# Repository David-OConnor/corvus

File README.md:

# Corvus: Small UAS flight controller firmware

todo: Fill out this README

This mainly exists as a code demo, although is mostly functional for quadcopter rate-control ("acro") flight, when paired with specific hardware. There is nascent code to support fixed-wing flight, but it is incomplete and untested.

It uses [RTIC](https://rtic.rs/2/book/en/) to manage control flow, via interrupts.

[Video of a flight](https://www.youtube.com/watch?v=sHvgl4OjA7A) (OSD not shown)

## Overview
This firmware is tied to specific hardware configurations. It runs on STM32G4 and STM32H743 flight controllers. (AnyLeaf boards). It requires specific hardware, currently:

 - ICM426xx IMU (SPI)
 - DPS310 barometeric altimeter (I2c)
 - UART GPS using the UBLOX protocol
 - MSP Displayport OSD (e.g. DJI O3, WTFOS etc)
 - DSHOT ESC motor controllers
 - ELRS (CRSF) controls (UART)
 - WIP support for CAN GPS, external AHRS, and controls

It is in either a flyable, or close to flyable state if paired with compatible hardware, using acro mode only. Code is written for semi-autonomous flight modes, but these are not working.

Its primary flight control model is attitude-based. Its acro mode is based on this as well, setting the attitude target based on rate controls, vice direct gyro reads. This results in higher latency than traditional gyro-based acro modes, but is less sensitive to tuning. It decouples control inputs from response.

See the [accompanying Preflight repo](https://github.com/David-OConnor/preflight/) for PC software that connects via USB to view system status, and configure the UAS.

See [the accompanying AHRS library](https://github.com/David-OConnor/ahrs), which it uses as a dependency,
for the attitude heading-reference system.

See [this DroneCAN library](https://github.com/David-OConnor/dronecan) for interaction with CAN peripherals.

See descriptions in individual modules for their function.

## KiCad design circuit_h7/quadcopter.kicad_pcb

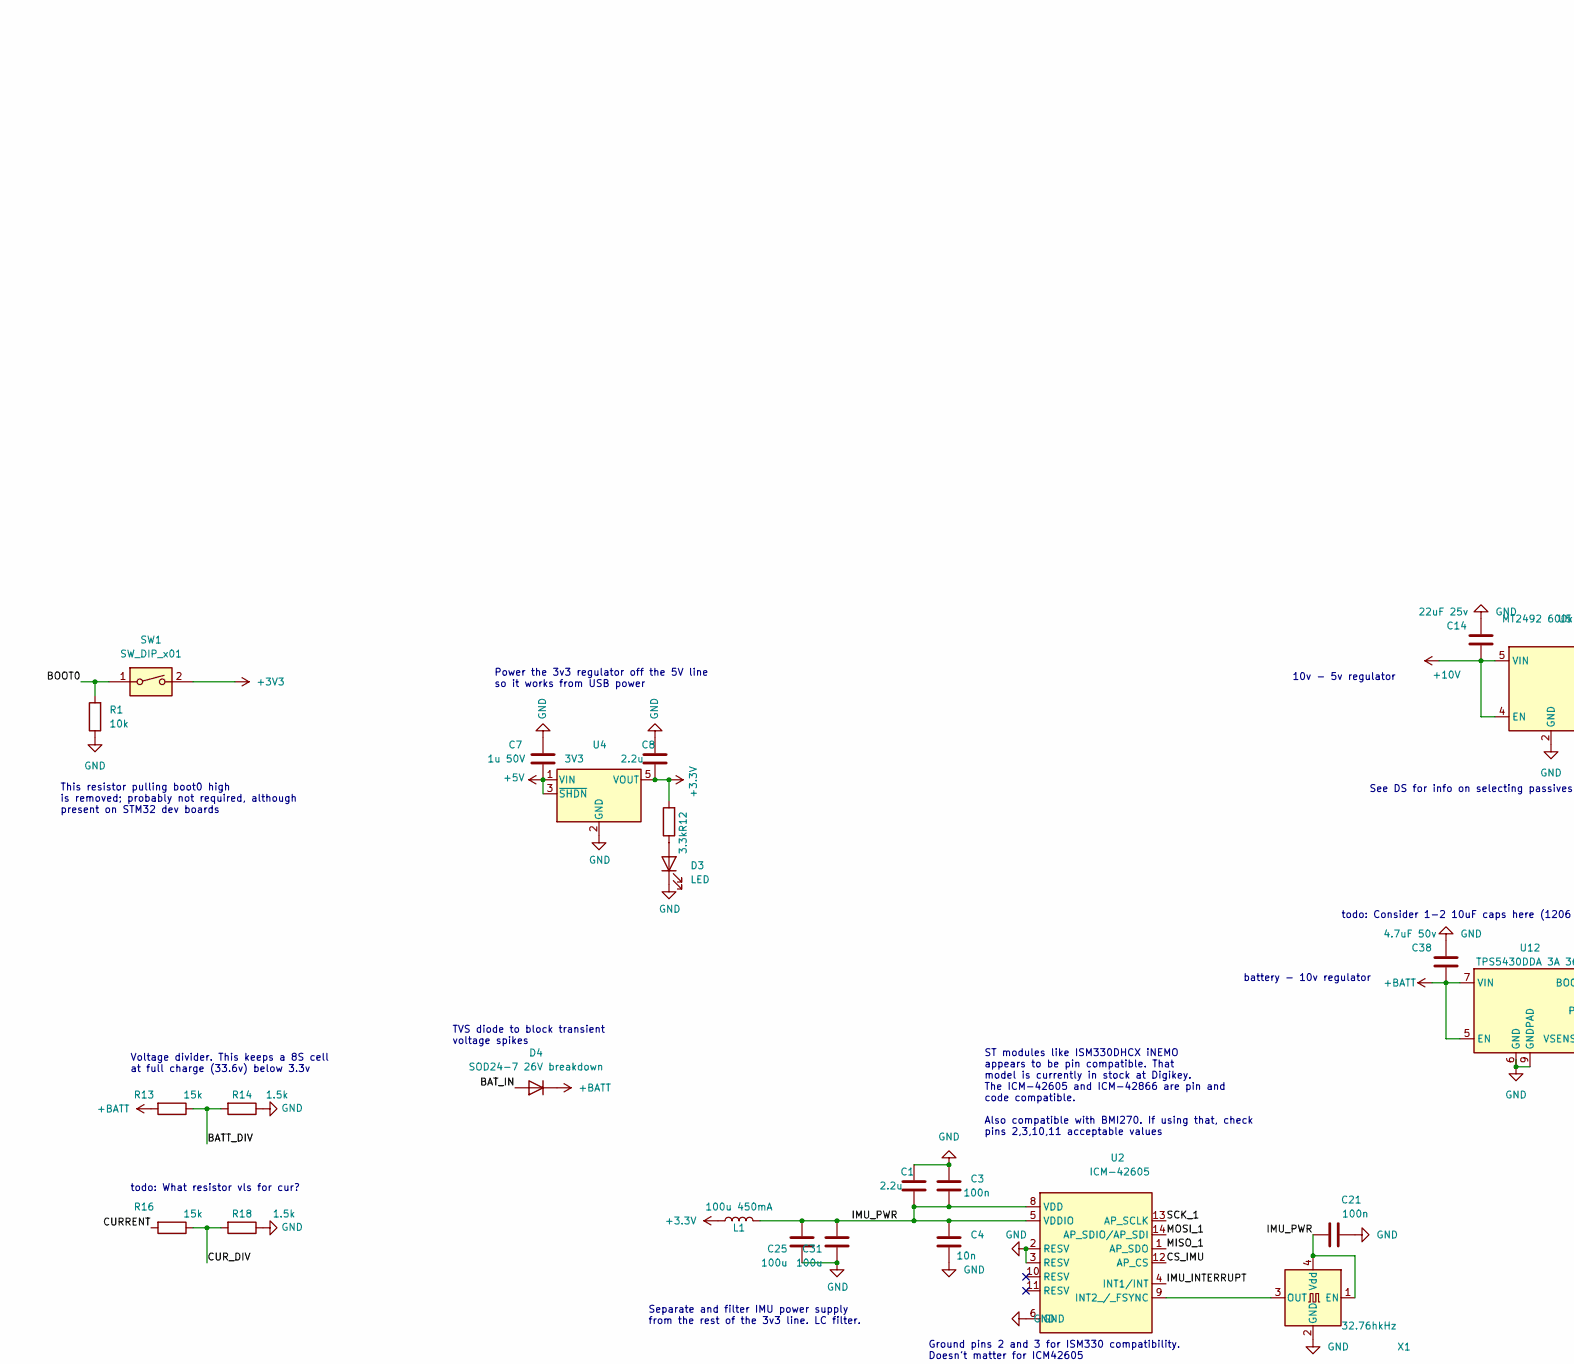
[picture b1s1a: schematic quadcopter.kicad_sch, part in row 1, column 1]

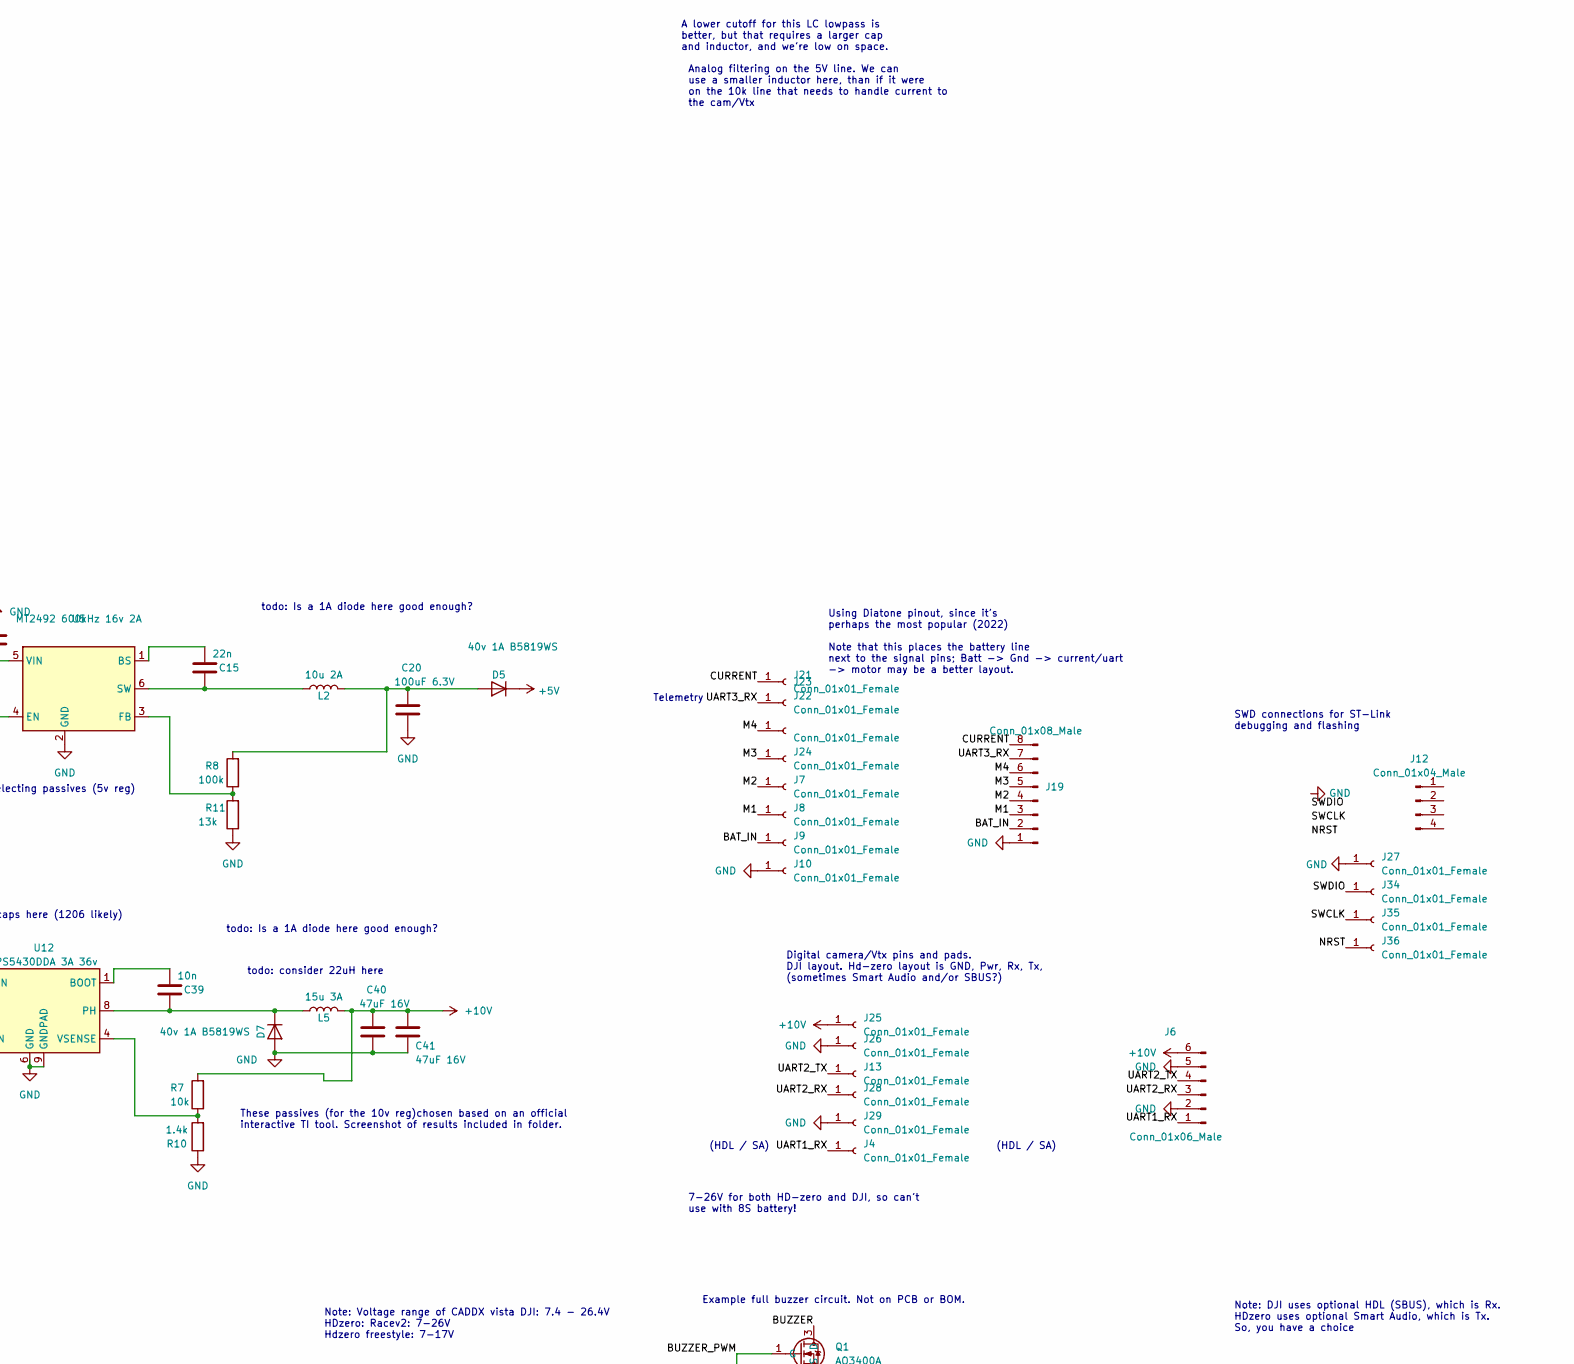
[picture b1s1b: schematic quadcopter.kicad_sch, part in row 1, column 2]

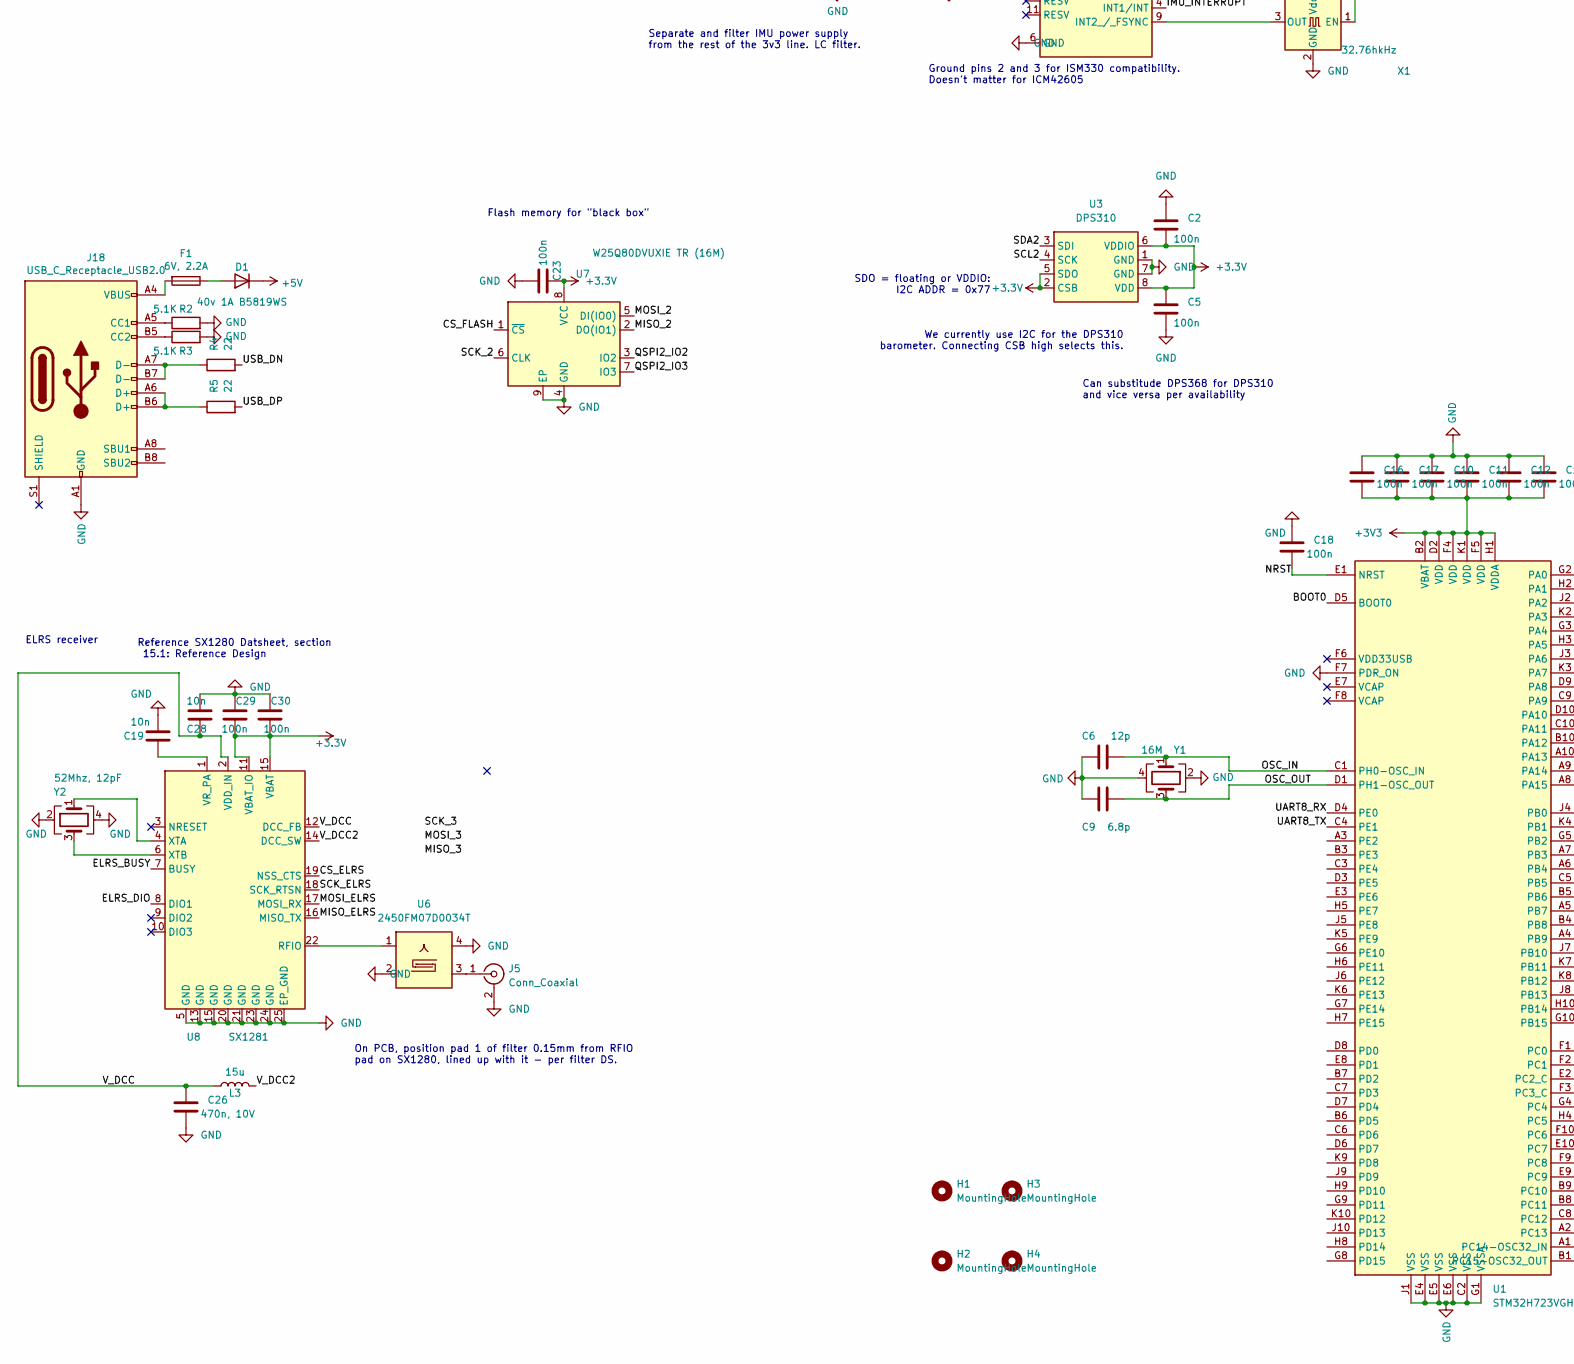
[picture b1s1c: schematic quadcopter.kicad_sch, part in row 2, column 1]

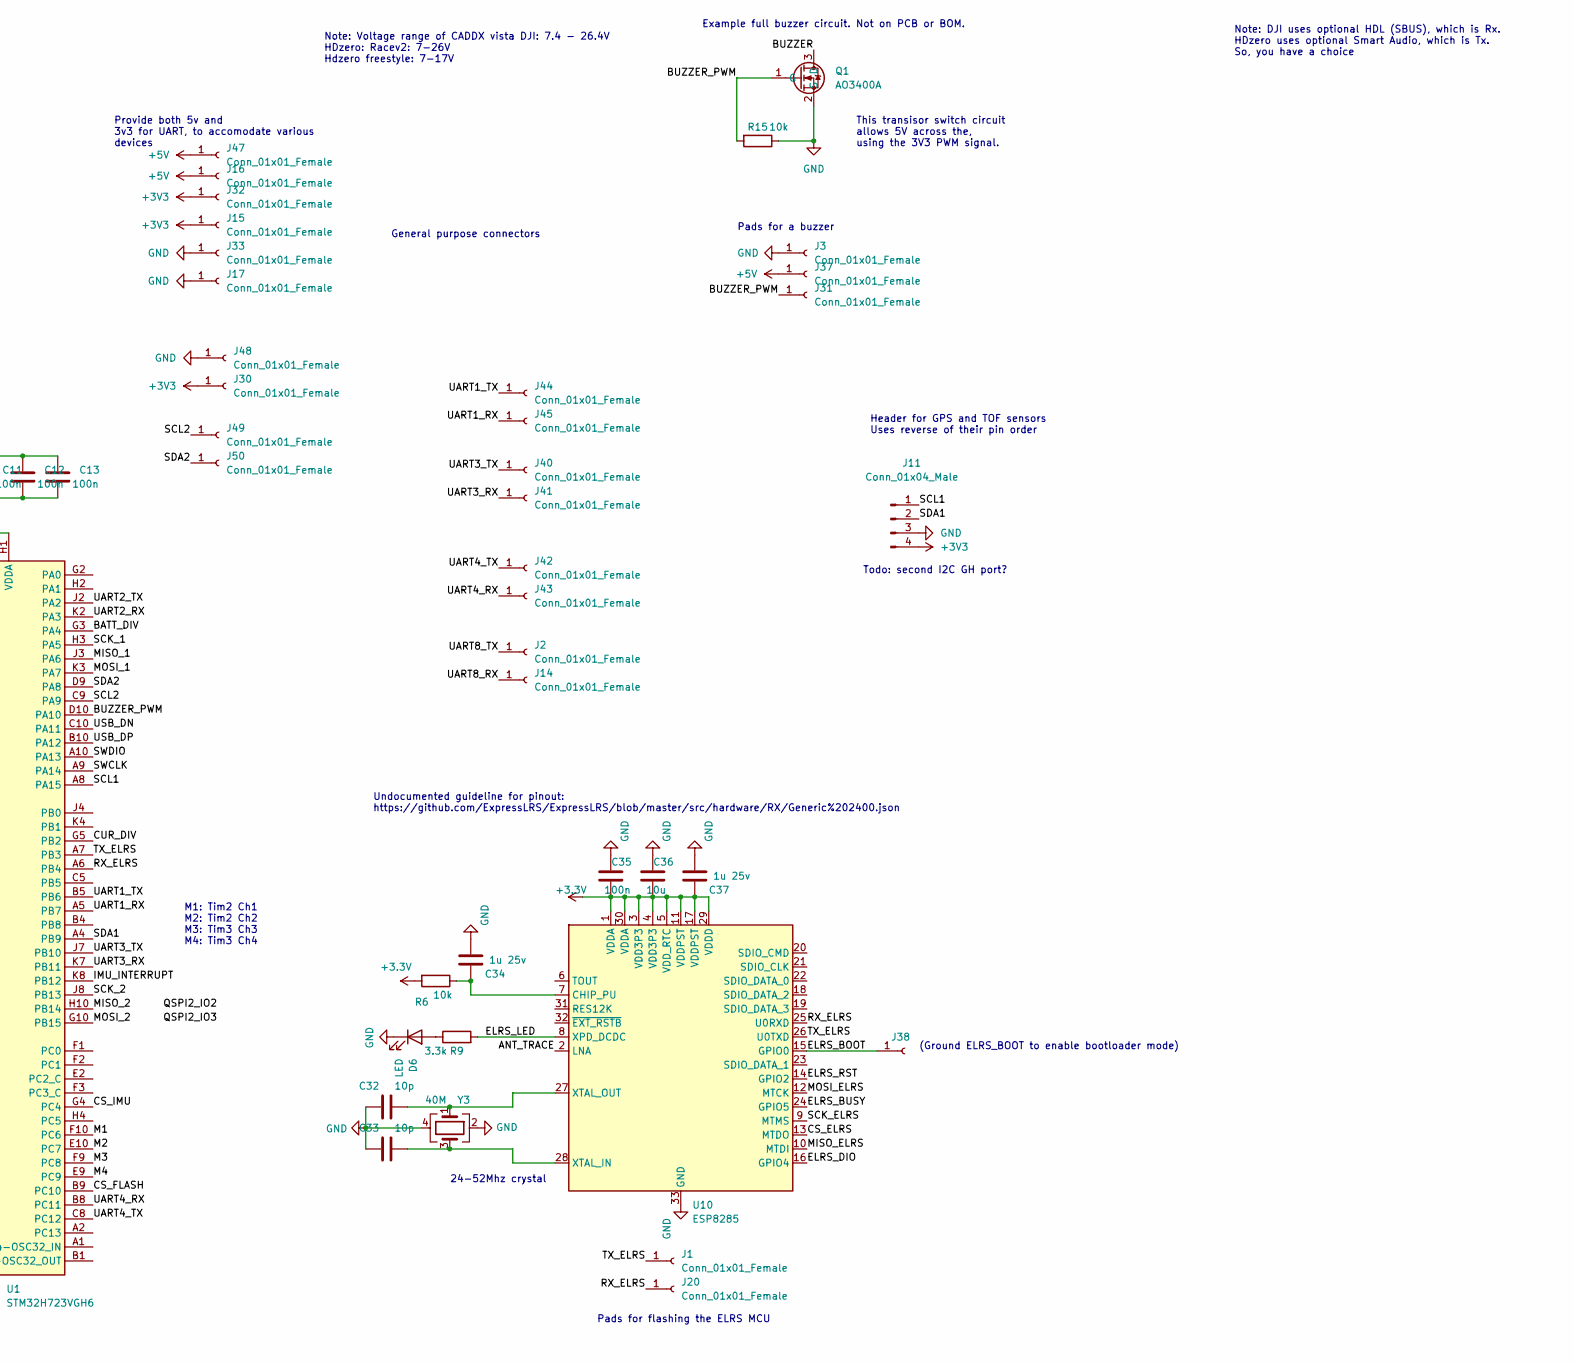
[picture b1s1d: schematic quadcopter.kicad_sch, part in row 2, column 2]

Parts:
C1, C8: 2.2u; C_0402_1005Metric; LCSC C12530
C2, C3, C5, C10, C11, C12, C13, C16, C17, C18, C21, C23, C29, C30, C35: 100n; C_0402_1005Metric; LCSC C1525
C4, C19, C28, C39: 10n; C_0402_1005Metric; LCSC C15195
C6: 12p; C_0402_1005Metric; LCSC C1547
C7: 1u 50V; C_0603_1608Metric; LCSC C15849
C9: 6.8p; C_0402_1005Metric; LCSC C1576
C14: 22uF 25v; C_0805_2012Metric; LCSC C602037
C15: 22n; C_0402_1005Metric; LCSC C1532
C20: 100uF 6.3V; C_1206_3216Metric; LCSC C15008
C25, C31: 100u; C_0805_2012Metric; LCSC C141660
C26: 470n, 10V; C_0402_1005Metric; LCSC C47339
C32, C33: 10p; C_0402_1005Metric; LCSC C32949
C34, C37: 1u 25v; C_0402_1005Metric; LCSC C52923
C36: 10u; C_0402_1005Metric; LCSC C15525
C38: 4.7uF 50v; C_0805_2012Metric; LCSC C98192
C40, C41: 47uF 16V; C_1210_3225Metric; LCSC C412625
D1, D5, D7: 40v 1A B5819WS; D_SOD-323; LCSC C22624
D3: LED; LED_0603_1608Metric; LCSC C205443
D4: SOD24-7 26V breakdown; D_SOD-323; Digikey 31-SD24-7TR-ND
D6: LED; LED_0603_1608Metric; LCSC C2286
F1: 6V, 2.2A; Fuse_0805_2012Metric; LCSC C70062
H1, H2, H3, H4: MountingHole; MountingHole_3.2mm_M3
J1, J20, J27, J34, J35, J36, J38: Conn_01x01_Female; TestPoint_Pad_1.0x1.0mm
J2, J3, J4, J7, J8, J9, J10, J13, J14, J15, J16, J17, J21, J22, J23, J24, J25, J26, J28, J29, J30, J31, J32, J33, J37, J40, J41, J42, J43, J44, J45, J47, J48, J49, J50: Conn_01x01_Female; TestPoint_Pad_2.0x2.0mm
J5: Conn_Coaxial; U.FL_Hirose_U.FL-R-SMT-1_Vertical; Part Hirose U.FL-R-SMT-1(80); LCSC C88374
J6: Conn_01x06_Male; JST_GH_SM06B-GHS-TB_1x06-1MP_P1.25mm_Horizontal; LCSC C160405
J11: Conn_01x04_Male; JST_GH_SM04B-GHS-TB_1x04-1MP_P1.25mm_Horizontal; LCSC C189895
J12: Conn_01x04_Male; JST PH staggered for 1x04 2mm
J18: USB_C_Receptacle_USB2.0; USB_C_Receptacle_XKB_U262-16XN-4BVC11; LCSC C167321
J19: Conn_01x08_Male; JST_GH_SM08B-GHS-TB_1x08-1MP_P1.25mm_Horizontal; LCSC C265111
L1: 100u 450mA; SMNR4020 inductor; LCSC C467068
L2: 10u 2A; L_Taiyo-Yuden_MD-4040; LCSC C98364
L3: 15u; L_0805_2012Metric; LCSC C154120
L5: 15u 3A; SLO0630H150MTT inductor; LCSC C182182
Q1: AO3400A; SOT-23; Digikey 785-1000-1-ND
R1, R6, R7, R15: 10k; R_0402_1005Metric; LCSC C25744
R2, R3: 5.1K; R_0402_1005Metric; LCSC C25905
R4, R5: 22; R_0402_1005Metric; LCSC C25092
R8: 100k; R_0402_1005Metric; LCSC C25741
R9, R12: 3.3k; R_0402_1005Metric; LCSC C25890
R10: 1.4k; R_0402_1005Metric; LCSC C39650
R11: 13k; R_0603_1608Metric; LCSC C22797
R13, R16: 15k; R_0402_1005Metric; LCSC C25756
R14, R18: 1.5k; R_0402_1005Metric; LCSC C25867
SW1: SW_DIP_x01; SW-SMD-2_3.6x6.0x8.0; LCSC C354946
U1: STM32H723VGH6; TFBGA-100_8x8mm_Layout10x10_P0.8mm
U2: ICM-42605; LGA-14_3x2.5mm_P0.5mm_LayoutBorder3x4y; Digikey 1428-1152-2-ND
U3: DPS310; Bosch_LGA-8_2x2.5mm_P0.65mm_ClockwisePinNumbering; Digikey DPS310XTSA1TR-ND
U4: 3V3; TSOT-23-5; Part NATLINEAR LN1134A332MR-G; LCSC C141419
U5: MT2492 600kHz 16v 2A; SOT-23-6; LCSC C89358
U6: 2450FM07D0034T; 2450FM07D0034; Mouser 609-2450FM07D0034T
U7: W25Q80DVUXIE TR (16M); WSON-8-1EP_6x5mm_P1.27mm_EP3.4x4.3mm
U8: SX1281; QFN-24-1EP_4x4mm_P0.5mm_EP2.6x2.6mm; Digikey SX1281IMLTRTTR-ND
U10: ESP8285; QFN-32-1EP_5x5mm_P0.5mm_EP3.45x3.45mm; LCSC C967019
U12: TPS5430DDA 3A 36v; TI_SO-PowerPAD-8_ThermalVias; LCSC C9864
X1: 32.76hkHz; Oscillator_SMD_EuroQuartz_XO32-4Pin_3.2x2.5mm; LCSC C253931
Y1: 16M; Crystal_SMD_2016-4Pin_2.0x1.6mm; LCSC C254300
Y2: 52Mhz, 12pF; Crystal_SMD_3225-4Pin_3.2x2.5mm; Digikey FL520WFMT1TR-ND
Y3: 40M; Crystal_SMD_2016-4Pin_2.0x1.6mm; LCSC C648973

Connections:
+5V: C7.2, D1.1 (K), D5.1 (K), J16.1, J37.1, J47.1, U4.1 (VIN), U4.3 (~SHDN)
+10V: C14.2, C40.1, C41.1, J6.6, J25.1, L5.2, R7.2, U5.4 (EN), U5.5 (VIN)
+BATT: C38.2, D4.1 (K), R13.2, U12.5 (EN), U12.7 (VIN)
/ANT_TRACE: U10.2 (LNA)
/BATT_DIV: R13.1, R14.2, U1.G3 (PA4)
/BAT_IN: D4.2 (A), J9.1, J19.2
/BOOT0: R1.2, SW1.1, U1.D5 (BOOT0)
/BUZZER_PWM: J31.1, Q1.1 (G), R15.2, U1.D10 (PA10)
/CS_ELRS: U8.19 (NSS_CTS), U10.13 (MTDO)
/CS_FLASH: U1.B9 (PC10), U7.1 (~CS)
/CS_IMU: U1.G4 (PC4), U2.12 (AP_CS)
/CURRENT: J19.8, J21.1, R16.2
/CUR_DIV: R16.1, R18.2, U1.G5 (PB2)
/ELRS_BOOT: J38.1, U10.15 (GPIO0)
/ELRS_BUSY: U8.7 (BUSY), U10.24 (GPIO5)
/ELRS_DIO: U8.8 (DIO1), U10.16 (GPIO4)
/ELRS_LED: R9.2, U10.8 (XPD_DCDC)
/ELRS_RST: U10.14 (GPIO2)
/IMU_INTERRUPT: U1.K8 (PB12), U2.4 (INT1/INT)
/IMU_PWR: C1.2, C3.2, C4.1, C21.1, C25.2, C31.2, L1.2, U2.5 (VDDIO), U2.8 (VDD), X1.1 (EN), X1.4 (Vdd)
/M1: J8.1, J19.3, U1.F10 (PC6)
/M2: J7.1, J19.4, U1.E10 (PC7)
/M3: J19.5, J24.1, U1.F9 (PC8)
/M4: J19.6, J23.1, U1.E9 (PC9)
/MISO_1: U1.J3 (PA6), U2.1 (AP_SDO)
/MISO_2: U1.H10 (PB14), U7.2 (DO(IO1))
/MISO_ELRS: U8.16 (MISO_TX), U10.10 (MTDI)
/MOSI_1: U1.K3 (PA7), U2.14 (AP_SDIO/AP_SDI)
/MOSI_2: U1.G10 (PB15), U7.5 (DI(IO0))
/MOSI_ELRS: U8.17 (MOSI_RX), U10.12 (MTCK)
/NRST: C18.2, J36.1, U1.E1 (NRST)
/OSC_IN: C6.2, U1.C1 (PH0-OSC_IN), Y1.1
/OSC_OUT: C9.2, U1.D1 (PH1-OSC_OUT), Y1.3
/QSPI2_IO2: U7.3 (IO2)
/QSPI2_IO3: U7.7 (IO3)
/RX_ELRS: J20.1, U1.A6 (PB4), U10.25 (U0RXD)
/SCK_1: U1.H3 (PA5), U2.13 (AP_SCLK)
/SCK_2: U1.J8 (PB13), U7.6 (CLK)
/SCK_ELRS: U8.18 (SCK_RTSN), U10.9 (MTMS)
/SCL1: J11.1, U1.A8 (PA15)
/SCL2: J49.1, U1.C9 (PA9), U3.4 (SCK)
/SDA1: J11.2, U1.A4 (PB9)
/SDA2: J50.1, U1.D9 (PA8), U3.3 (SDI)
/SWCLK: J35.1, U1.A9 (PA14)
/SWDIO: J34.1, U1.A10 (PA13)
/TX_ELRS: J1.1, U1.A7 (PB3), U10.26 (U0TXD)
/UART1_RX: J4.1, J6.1, J45.1, U1.A5 (PB7)
/UART1_TX: J44.1, U1.B5 (PB6)
/UART2_RX: J6.3, J28.1, U1.K2 (PA3)
/UART2_TX: J6.4, J13.1, U1.J2 (PA2)
/UART3_RX: J19.7, J22.1, J41.1, U1.K7 (PB11)
/UART3_TX: J40.1, U1.J7 (PB10)
/UART4_RX: J43.1, U1.B8 (PC11)
/UART4_TX: J42.1, U1.C8 (PC12)
/UART8_RX: J14.1, U1.D4 (PE0)
/UART8_TX: J2.1, U1.C4 (PE1)
/USB_DN: R4.2, U1.C10 (PA11)
/USB_DP: R5.2, U1.B10 (PA12)
/V_DCC: C26.1, C28.2, L3.1, U8.2 (VDD_IN), U8.12 (DCC_FB)
/V_DCC2: L3.2, U8.14 (DCC_SW)
unnamed: C15.1, U5.1 (BS)
unnamed: C15.2, L2.1, U5.6 (SW)
unnamed: C19.2, U8.1 (VR_PA)
unnamed: C20.1, D5.2 (A), L2.2, R8.2
unnamed: C32.2, U10.27 (XTAL_OUT), Y3.1
unnamed: C33.2, U10.28 (XTAL_IN), Y3.3
unnamed: C34.1, R6.1, U10.7 (CHIP_PU)
unnamed: C39.1, U12.1 (BOOT)
unnamed: C39.2, D7.1 (K), L5.1, U12.8 (PH)
unnamed: D1.2 (A), F1.1
unnamed: D3.2 (A), R12.1
unnamed: D6.2 (A), R9.1
unnamed: F1.2, J18.A4 (VBUS), J18.A9 (VBUS), J18.B4 (VBUS), J18.B9 (VBUS)
unnamed: J5.1 (In), U6.3
unnamed: J18.A5 (CC1), R2.1
unnamed: J18.A6 (D+), J18.B6 (D+), R5.1
unnamed: J18.A7 (D-), J18.B7 (D-), R4.1
unnamed: J18.B5 (CC2), R3.1
unnamed: R7.1, R10.2, U12.4 (VSENSE)
unnamed: R8.1, R11.2, U5.3 (FB)
unnamed: U2.9 (INT2_/_FSYNC), X1.3 (OUT)
unnamed: U6.1, U8.22 (RFIO)
unnamed: U8.4 (XTA), Y2.1
unnamed: U8.6 (XTB), Y2.3

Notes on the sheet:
(HDL / SA)
todo: What resistor vls for cur?
These passives (for the 10v reg)chosen based on an official interactive TI tool. Screenshot of results included in folder.
Todo: second I2C GH port?
Telemetry
(Ground ELRS_BOOT to enable bootloader mode)
24-52Mhz crystal
M1: Tim2 Ch1 M2: Tim2 Ch2 M3: Tim3 Ch3 M4: Tim3 Ch4
General purpose connectors
Voltage divider. This keeps a 8S cell at full charge (33.6v) below 3.3v
todo: Is a 1A diode here good enough?
Digital camera/Vtx pins and pads. DJI layout. Hd-zero layout is GND, Pwr, Rx, Tx, (sometimes Smart Audio and/or SBUS?)
On PCB, position pad 1 of filter 0.15mm from RFIO pad on SX1280, lined up with it - per filter DS.
Reference SX1280 Datsheet, section 15.1: Reference Design
We currently use I2C for the DPS310 barometer. Connecting CSB high selects this.
Separate and filter IMU power supply from the rest of the 3v3 line. LC filter.
This transisor switch circuit allows 5V across the, using the 3V3 PWM signal.
Provide both 5v and 3v3 for UART, to accomodate various devices
TVS diode to block transient voltage spikes
todo: consider 22uH here
10v - 5v regulator
ST modules like ISM330DHCX iNEMO appears to be pin compatible. That model is currently in stock at Digikey. The ICM-42605 and ICM-42866 are pin and code compatible. Also compatible with BMI270. If using that, check pins 2,3,10,11 acceptable values
Example full buzzer circuit. Not on PCB or BOM.
Pads for flashing the ELRS MCU
This resistor pulling boot0 high is removed; probably not required, although present on STM32 dev boards
SWD connections for ST-Link debugging and flashing
todo: Consider 1-2 10uF caps here (1206 likely)
Undocumented guideline for pinout: https://github.com/ExpressLRS/ExpressLRS/blob/master/src/hardware/RX/Generic%202400.json
Ground pins 2 and 3 for ISM330 compatibility. Doesn't matter for ICM42605
Using Diatone pinout, since it's perhaps the most popular (2022) Note that this places the battery line next to the signal pins; Batt -> Gnd -> current/uart -> motor may be a better layout.
See DS for info on selecting passives (5v reg)
A lower cutoff for this LC lowpass is better, but that requires a larger cap and inductor, and we're low on space.
Analog filtering on the 5V line. We can use a smaller inductor here, than if it were on the 10k line that needs to handle current to the cam/Vtx
battery - 10v regulator
Flash memory for "black box"
Header for GPS and TOF sensors Uses reverse of their pin order
Note: Voltage range of CADDX vista DJI: 7.4 - 26.4V HDzero: Racev2: 7-26V Hdzero freestyle: 7-17V
ELRS receiver
Note: DJI uses optional HDL (SBUS), which is Rx. HDzero uses optional Smart Audio, which is Tx. So, you have a choice
Pads for a buzzer

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
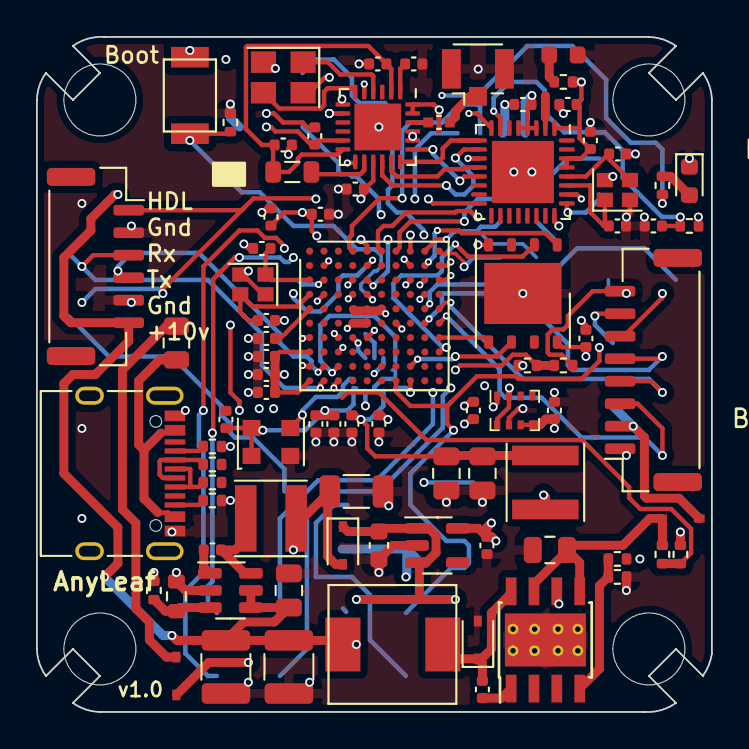
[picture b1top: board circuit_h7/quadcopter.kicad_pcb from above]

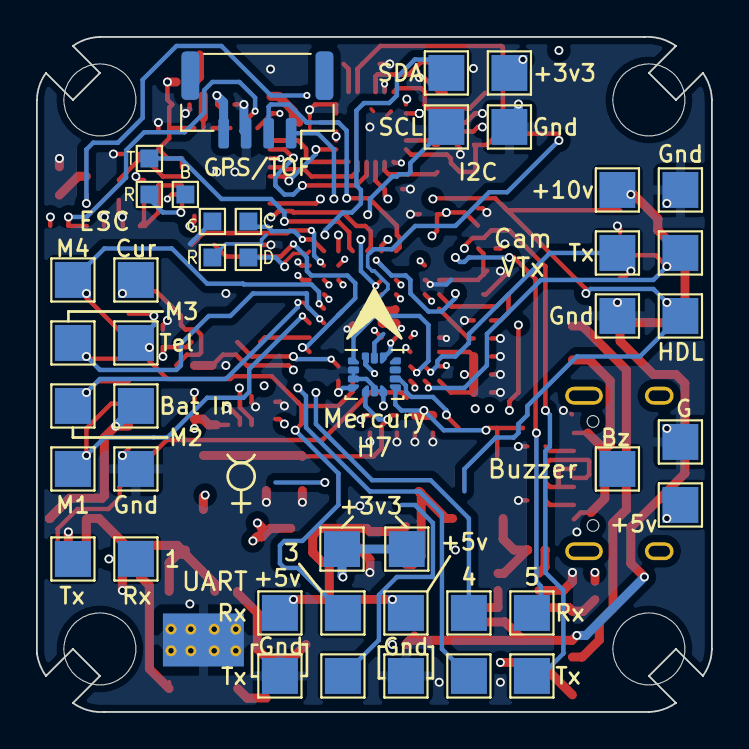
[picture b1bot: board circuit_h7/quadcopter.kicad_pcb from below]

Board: 4 copper layers, 37.5 x 37.5 mm, 131 parts (44 on the bottom side), 82 nets.

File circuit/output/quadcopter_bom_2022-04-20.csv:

Comment,Designator,Footprint,LCSC
2.2u,"C1,C8,C22",Capacitor_SMD:C_0402_1005Metric,C12530
10uF 50V,C14,Capacitor_SMD:C_0805_2012Metric,C440198
100n,"C2,C3,C5,C10,C11,C12,C13,C16,C17,C18,C23,C29,C30",Capacitor_SMD:C_0402_1005Metric,C1525
22uF 25V,C20,Capacitor_SMD:C_0805_2012Metric,C45783
10nF 50V,C21,Capacitor_SMD:C_0402_1005Metric,C15195
"470n, 10V",C26,Capacitor_SMD:C_0402_1005Metric,C47339
100u,C31,Capacitor_SMD:C_0805_2012Metric,C141660
10n,"C4,C19,C28",Capacitor_SMD:C_0402_1005Metric,C15195
12p,C6,Capacitor_SMD:C_0402_1005Metric,C1547
1u 50V,"C7,C15",Capacitor_SMD:C_0603_1608Metric,C15849
6.8p,C9,Capacitor_SMD:C_0402_1005Metric,C1576
40v 1A B5819WS,"D1,D2,D5",Diode_SMD:D_SOD-323,C22624
LED,D3,LED_SMD:LED_0603_1608Metric,C205443
SOD24-7 26V breakdown,D4,Diode_SMD:D_SOD-323,
"6V, 2.2A",F1,Fuse:Fuse_0805_2012Metric,C70062
MountingHole,"H1,H2,H3,H4,H5,H6,H7,H8",MountingHole:MountingHole_3.2mm_M3,
MountingHole_Pad,"H9,H10,H11,H12",Anyleaf_Shared:Mouse bites_7mm,
Conn_01x01_Female,"J1,J2,J34",TestPoint:TestPoint_Pad_1.0x1.0mm,
USB_C_Receptacle_USB2.0,J18,Connector_USB:USB_C_Receptacle_XKB_U262-16XN-4BVC11,C167321
Conn_01x08_Male,J19,Connector_JST:JST_SH_SM08B-SRSS-TB_1x08-1MP_P1.00mm_Horizontal,C160407
Conn_01x01_Female,"J3,J4,J13,J25,J26,J28,J29,J31,J37",TestPoint:TestPoint_Pad_1.5x1.5mm,
Conn_Coaxial,J5,Connector_Coaxial:U.FL_Hirose_U.FL-R-SMT-1_Vertical,C88374
Conn_01x01_Female,"J7,J8,J9,J10,J15,J16,J17,J21,J22,J23,J24,J30,J32,J33,J40,J41,J42,J43,J44,J45,J46,J47,J48,J49,J50",TestPoint:TestPoint_Pad_2.0x2.0mm,
100u 450mA,L1,Anyleaf_Shared:SMNR4020 inductor,C467068
15u,L3,Inductor_SMD:L_0805_2012Metric,C154120
22u 900mA,L4,Anyleaf_Shared:SMNR4020 inductor,C88254
10k,R1,Resistor_SMD:R_0402_1005Metric,C25744
1k,R12,Resistor_SMD:R_0402_1005Metric,C25741
15k,"R13,R16",Resistor_SMD:R_0402_1005Metric,C25756
1.5k,"R14,R18",Resistor_SMD:R_0402_1005Metric,C25867
5.1K,"R2,R3",Resistor_SMD:R_0402_1005Metric,C25905
22,"R4,R5",Resistor_SMD:R_0402_1005Metric,C25092
3.3K,R7,Resistor_SMD:R_0402_1005Metric,C25890
300,R8,Resistor_SMD:R_0402_1005Metric,C25102
SW_DIP_x01,SW1,Anyleaf_Shared:SW-SMD-2_3.6x6.0x8.0,C354946
STM32G474CEU6,U1,Package_DFN_QFN:QFN-48-1EP_7x7mm_P0.5mm_EP5.6x5.6mm,C529356
ICM-42605,U2,Package_LGA:LGA-14_3x2.5mm_P0.5mm_LayoutBorder3x4y,C2655099
DPS310,U3,Package_LGA:Bosch_LGA-8_2x2.5mm_P0.65mm_ClockwisePinNumbering,
3V3,U4,Package_TO_SOT_SMD:TSOT-23-5,C141419
"EUP3458 1.2A, 30V max input, adj output",U5,Package_TO_SOT_SMD:TSOT-23-6,C89300
2450FM07D0034T,U6,Anyleaf_Shared:2450FM07D0034,
W25Q80DVUXIE TR (16M),U7,Anyleaf_Shared:USON-8_2.0x3.0mm_P0.5mm,
SX1281,U8,Package_DFN_QFN:QFN-24-1EP_4x4mm_P0.5mm_EP2.6x2.6mm,C2151551
"5v, 500mA",U9,Package_TO_SOT_SMD:TSOT-23-5,C13417
16M,Y1,Crystal:Crystal_SMD_2016-4Pin_2.0x1.6mm,C254300
"52Mhz, 12pF",Y2,Crystal:Crystal_SMD_2016-4Pin_2.0x1.6mm,
